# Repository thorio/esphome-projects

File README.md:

This is a loose collection of my esphome projects, including pcbs, schematics, CAD drawings and firmware where applicable.

Most don't have BOMs or assembly instructions unfortunately, as it would just eat up too much time.

Open an issue if you have questions.

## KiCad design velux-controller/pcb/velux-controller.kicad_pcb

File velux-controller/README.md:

# ESPHome Velux Controller

This project modifies a Velux KLI 310 or similar remote control to integrate with home assistant.
It replaces the back panel of the original remote, powers it from the wall, and can report state back to home assistant even if you press the physical buttons.

Installing it on the remote only requires removing the back and batteries, soldering 5 wires and plugging it into the control board. This process is nondestructive and reversible.

It runs on anywhere between 5V and 12V, though 5V is preferred.

## Bill of Materials

- 1x ESP-12F module
	([Mouser](https://eu.mouser.com/ProductDetail/Adafruit/2491?qs=N%2F3wi2MvZWDVFv7HwruvGQ%3D%3D),
	[AliExpress](https://www.aliexpress.com/item/1005004495916418.html))
- 1x SOT223 AMS1117-3.3 linear voltage regulator
	([DigiKey](https://www.digikey.com/en/products/detail/texas-instruments/TLV1117LV33DCYR/2666508),
	[AliExpress](https://www.aliexpress.com/item/1005004529378722.html))
- 3x SOT23 MMBT3904 transistor
	([DigiKey](https://www.digikey.com/en/products/detail/diotec-semiconductor/MMBT3904/20391048),
	[AliExpress](https://www.aliexpress.com/item/1005002334131697.html))
- 8x 0603 10kΩ resistor
	([DigiKey](https://www.digikey.com/en/products/detail/stackpole-electronics-inc/RMCF0603FT10K0/1761235),
	[AliExpress](https://www.aliexpress.com/item/32867298442.html))
- 6x 0603 1kΩ resistor
	([DigiKey](https://www.digikey.com/en/products/detail/stackpole-electronics-inc/RMCF0603FT1K00/1761077),
	[AliExpress](https://www.aliexpress.com/item/32867298442.html))
- 2x 0805 100nF ceramic capacitor
	([DigiKey](https://www.digikey.com/en/products/detail/samsung-electro-mechanics/CL21B104KACNNNC/3886757),
	[AliExpress](https://www.aliexpress.com/item/32964553793.html))
- 1x SMA 22μF tantalum capacitor
	([DigiKey](https://www.digikey.com/en/products/detail/kemet/T491A226M010AT/818553),
	[AliExpress](https://www.aliexpress.com/item/1005006136419609.html))
- 2x PTS820 tactile switch
	([DigiKey](https://www.digikey.com/en/products/detail/cit-relay-and-switch/CS1213AGF160/16607723),
	[AliExpress](https://www.aliexpress.com/item/1005004307665595.html))
- 1x DC-005 jack
	([DigiKey](https://www.digikey.com/en/products/detail/tensility-international-corp/54-00166/10459294),
	[AliExpress](https://www.aliexpress.com/item/4001206395694.html))
- 1x male pin header 1x4 2.54mm pitch
	([AliExpress](https://www.aliexpress.com/item/4000857385112.html))
- 1x 2Pin JST-XH connector pair, right angle
	([DigiKey](https://www.digikey.com/en/products/detail/jst-sales-america-inc/S2B-XH-A-1/9961922),
	AliExpress [assortment](https://www.aliexpress.com/item/1005006498660940.html) + [right angle](https://www.aliexpress.com/item/1005004067623293.html))
- 1x 3Pin JST-XH connector pair, right angle
	([DigiKey](https://www.digikey.com/en/products/detail/jst-sales-america-inc/S3B-XH-A-1/1556255),
	AliExpress [assortment](https://www.aliexpress.com/item/1005006498660940.html) + [right angle](https://www.aliexpress.com/item/1005004067623293.html))
- spare wire + JST-XH crimps
	([AliExpress assortment](https://www.aliexpress.com/item/1005006498660940.html))
- 4x M2x6mm coarse thread screws, pan head
	([AliExpress](https://www.aliexpress.com/item/33043885403.html))
- 4x M2 paper washers
	([AliExpress](https://www.aliexpress.com/item/1005003052657995.html))

I didn't need these, but you can add them if your ESP is unhappy with the supply voltage:

> Note: It isn't super obvious from the footprints, but these additional capacitors are supposed to mount horizontally against the board facing toward the bottom. If mounted vertically they may prevent the case from being closed.

- 1x 470μF >=5V electrolytic capacitor, 2mm pitch
	([DigiKey](https://www.digikey.com/en/products/detail/wurth-elektronik/860010273011/5726952),
	[AliExpress assortment](https://www.aliexpress.com/item/1940215752.html))
- 1x 10μF >=16V electrolytic capacitor, 1.5mm pitch
	([DigiKey](https://www.digikey.com/en/products/detail/nichicon/UVR1C100MDD6TP/4328964),
	[AliExpress assortment](https://www.aliexpress.com/item/1940215752.html))

## Attribution
Thanks to these fine people for their research on how to interface with the remote control:
- https://ottelo.jimdofree.com/velux-integra-esp8266/
- https://www.reddit.com/r/homeassistant/comments/pzhkia/hack_velux_kli3xx_to_use_blinds_without_gateway/

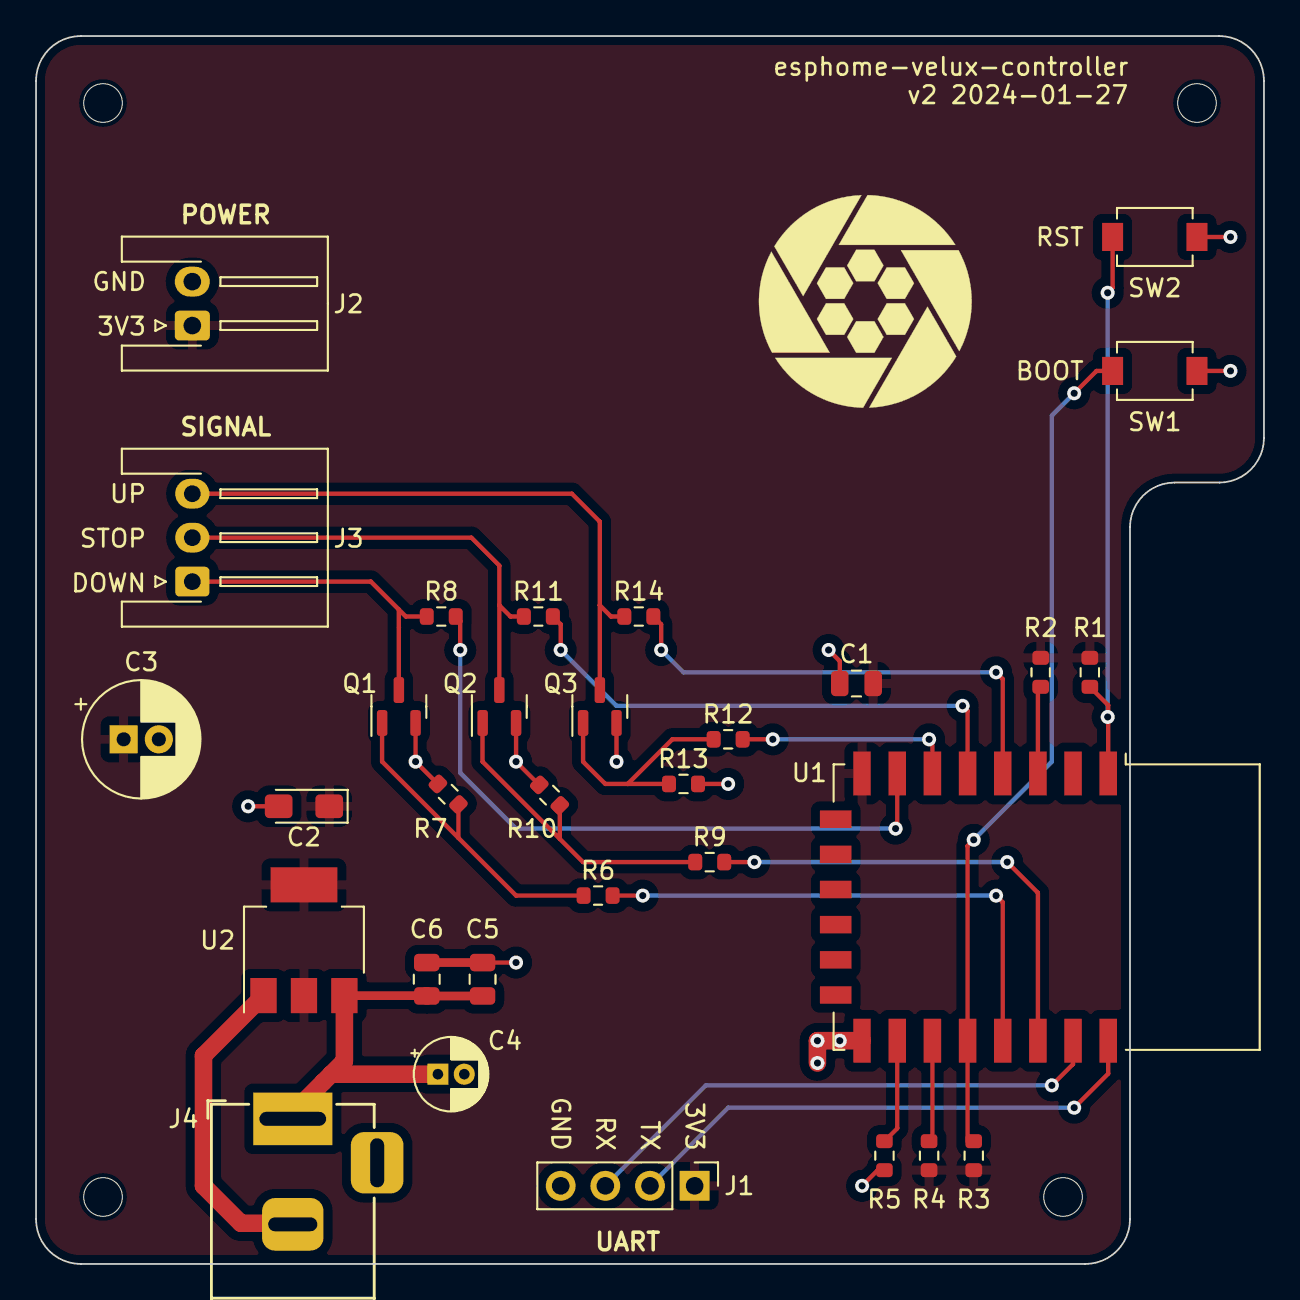
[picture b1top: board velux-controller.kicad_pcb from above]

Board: 2 copper layers, 69.9 x 69.8 mm, 35 parts (0 on the bottom side), 22 nets.

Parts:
C1, C6: 0.1μF; C_0805_2012Metric
C2: 22μF; CP_EIA-3216-10_Kemet-I_Pad1.58x1.35mm_HandSolder
C3: 470μF; CP_Radial_D6.5mm_P2.00mm
C4: 10μF; CP_Radial_D4.0mm_P1.50mm
C5: 10μF; C_0805_2012Metric
H1, H2, H3, H4: MountingHole; MountingHole_2.2mm_M2
J1: UART; PinHeader_1x04_P2.54mm_Vertical
J2: POWER; JST_XH_S2B-XH-A-1_1x02_P2.50mm_Horizontal
J3: SIGNAL; JST_XH_S3B-XH-A-1_1x03_P2.50mm_Horizontal
J4: PWR; DC_barrel_jack_2.1mm
Q1, Q2, Q3: MMBT3904; SOT-23
R1, R2, R3, R4, R5, R7, R10, R13: 10K; R_0603_1608Metric
R6, R8, R9, R11, R12, R14: 1K; R_0603_1608Metric
SW1: BOOT; SW_PTS820
SW2: RST; SW_PTS820
U1: ESP-12F; ESP-12E
U2: AMS1117-3.3; SOT-223-3_TabPin2

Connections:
+3.3V: C1.2, C2.1, C3.1, J1.1, J2.1, R1.2, R2.2, R3.2, R4.2, U1.8 (VCC), U2.2 (VO)
/EN: R2.1, U1.3 (EN)
/GPIO0: R3.1, SW1.2, U1.18 (GPIO0)
/GPIO2: R4.1, U1.17 (GPIO2)
/GPIO4: R6.2, U1.19 (GPIO4)
/GPIO5: R9.2, U1.20 (GPIO5)
/GPIO12: R12.2, U1.6 (GPIO12)
/GPIO13: R8.2, U1.7 (GPIO13)
/GPIO14: R11.2, U1.5 (GPIO14)
/GPIO15: R5.2, U1.16 (GPIO15)
/GPIO16: R14.2, U1.4 (GPIO16)
/LINE_DOWN: J3.1, Q1.3 (C), R8.1
/LINE_STOP: J3.2, Q2.3 (C), R11.1
/LINE_UP: J3.3, Q3.3 (C), R14.1
/RST: R1.1, SW2.2, U1.1 (~RST)
/RXD: J1.3, U1.21 (GPIO3/RXD)
/TXD: J1.2, U1.22 (GPIO1/TXD)
GND: C1.1, C2.2, C3.2, C4.2, C5.1, C6.1, J1.4, J2.2, J4.2, Q1.2 (E), Q2.2 (E), Q3.2 (E), R5.1, R7.2, R10.2, R13.2, SW1.1, SW2.1, U1.15 (GND), U2.1 (GND)
unnamed: Q1.1 (B), R6.1, R7.1
unnamed: Q2.1 (B), R9.1, R10.1
unnamed: Q3.1 (B), R12.1, R13.1
VCC: C4.1, C5.2, C6.2, J4.1, U2.3 (VI)

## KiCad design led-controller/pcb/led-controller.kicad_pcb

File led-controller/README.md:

# ESPHome LED Controller

Controls either individually addressible or single-color "dumb" LED strips, with an optional button or rotary encoder.
This means I effectively get four different controller options in one PCB order.

It can use either 12V or 5V LED strips, running the controller off the same power supply as the LEDs.

### WARNING: I didn't properly engineer this, so I don't know how much current it can safely push. Use at your own risk.

### Variants

Depending on the configuration, different parts must be printed and different components soldered to the board:

**Input**: Solder either the push-button or the rotary encoder, and print the appropriate covers for the housing.

**Output**: Solder either:
- the mosfet U1 for PWM control of "dumb" LEDs or
- the resistor R6 and the jumper JP1 for controlling individually addressible LEDs.

Depending on the configuration chosen, the firmware must be modified as well. See the comments in `firmware.yml`.

NOTE: I had to rip out some of the reference models from the Fusion 360 CAD drawings because I don't have the rights to them.
This leaves the references all jumbled, sorry about that.

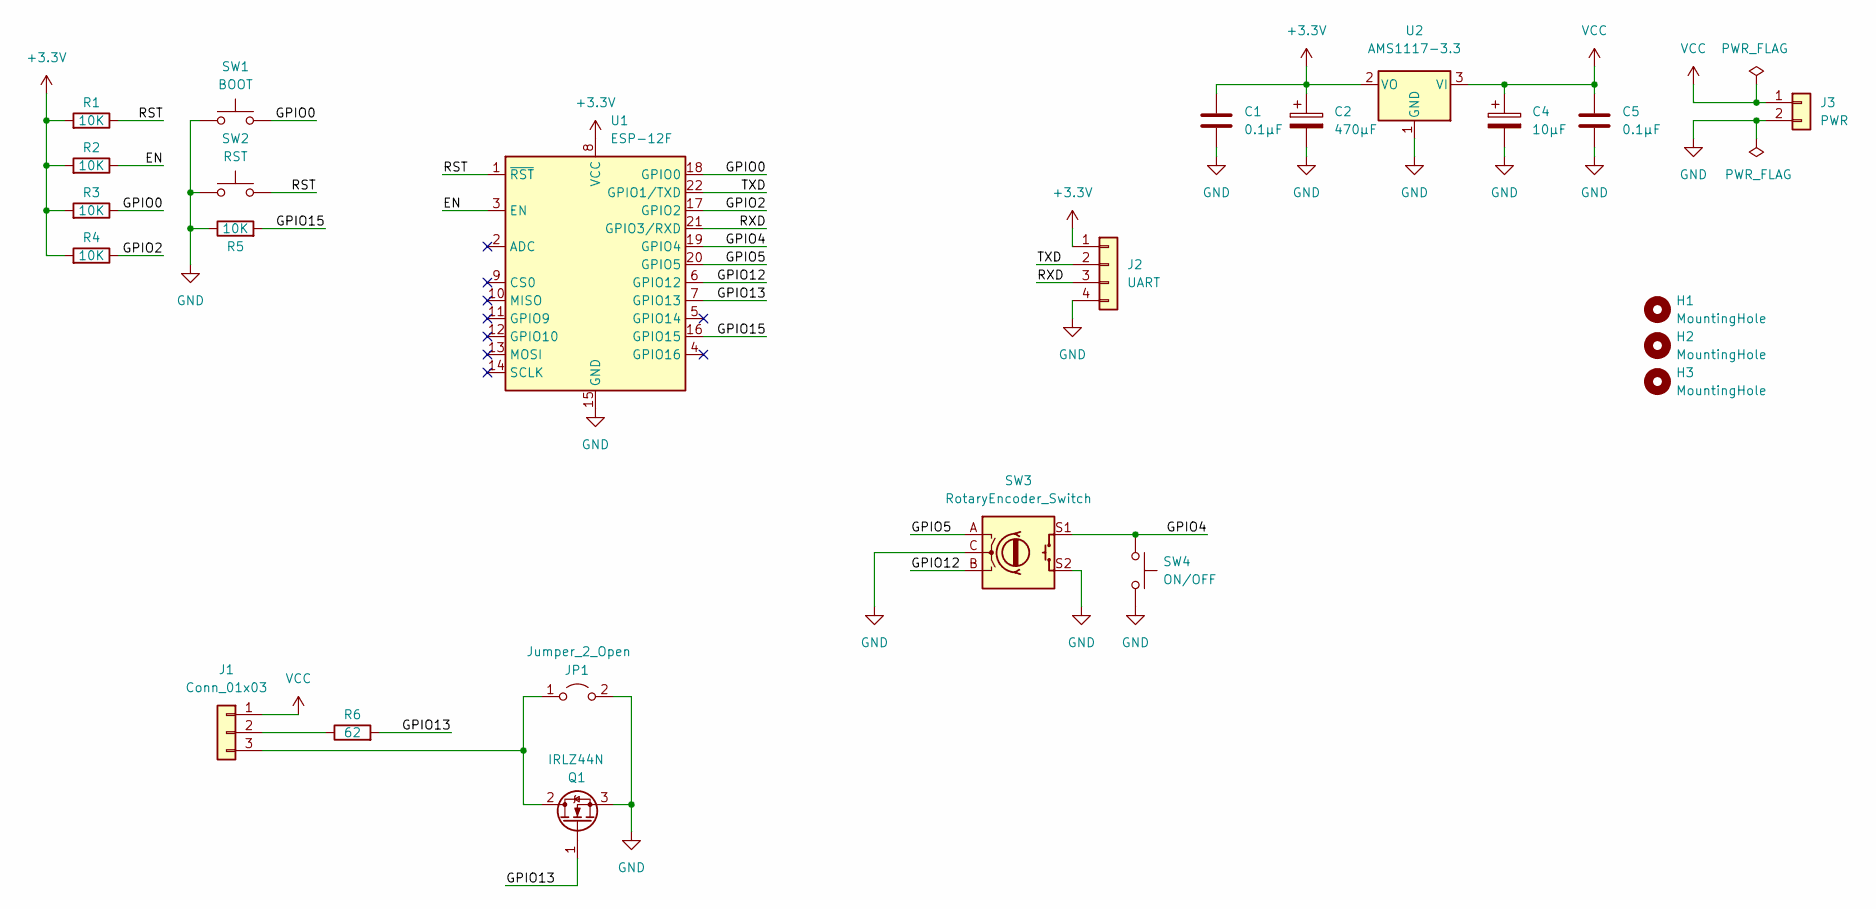
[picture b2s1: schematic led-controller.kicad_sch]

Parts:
C1, C5: 0.1μF; C_0805_2012Metric
C2: 470μF; CP_Radial_D6.5mm_P2.00mm
C4: 10μF; CP_Radial_D4.0mm_P1.50mm
H1, H2, H3: MountingHole; MountingHole_2.2mm_M2
J1: Conn_01x03; TerminalBlock_KF301-3P-5mm
J2: UART; PinHeader_1x04_P2.54mm_Vertical
J3: PWR; TerminalBlock_KF301-2P-5mm
JP1: Jumper_2_Open; SolderWire-1.5sqmm_1x02_P6mm_D1.7mm_OD3mm
Q1: IRLZ44N; TO-220-3_Horizontal_TabDown
R1, R2, R3, R4, R5: 10K; R_0603_1608Metric
R6: 62; R_0603_1608Metric
SW1: BOOT; SW_PTS820
SW2: RST; SW_PTS820
SW3: RotaryEncoder_Switch; RotaryEncoder_Alps_EC11E-Switch_Vertical_H20mm
SW4: ON/OFF; SW_SPST_TL3342
U1: ESP-12F; ESP-12E
U2: AMS1117-3.3; SOT-223-3_TabPin2

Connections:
+3.3V: C1.2, C2.1, J2.1, R1.2, R2.2, R3.2, R4.2, U1.8 (VCC), U2.2 (VO)
/EN: R2.1, U1.3 (EN)
/GPIO0: R3.1, SW1.2, U1.18 (GPIO0)
/GPIO2: R4.1, U1.17 (GPIO2)
/GPIO4: SW3.S1, SW4.1, U1.19 (GPIO4)
/GPIO5: SW3.A, U1.20 (GPIO5)
/GPIO12: SW3.B, U1.6 (GPIO12)
/GPIO13: Q1.1 (G), R6.2, U1.7 (GPIO13)
/GPIO15: R5.2, U1.16 (GPIO15)
/RST: R1.1, SW2.2, U1.1 (~RST)
/RXD: J2.3, U1.21 (GPIO3/RXD)
/TXD: J2.2, U1.22 (GPIO1/TXD)
GND: C1.1, C2.2, C4.2, C5.1, J2.4, J3.2, JP1.2 (B), Q1.3 (S), R5.1, SW1.1, SW2.1, SW3.C, SW3.S2, SW4.2, U1.15 (GND), U2.1 (GND)
unnamed: J1.2, R6.1
unnamed: J1.3, JP1.1 (A), Q1.2 (D)
VCC: C4.1, C5.2, J1.1, J3.1, U2.3 (VI)

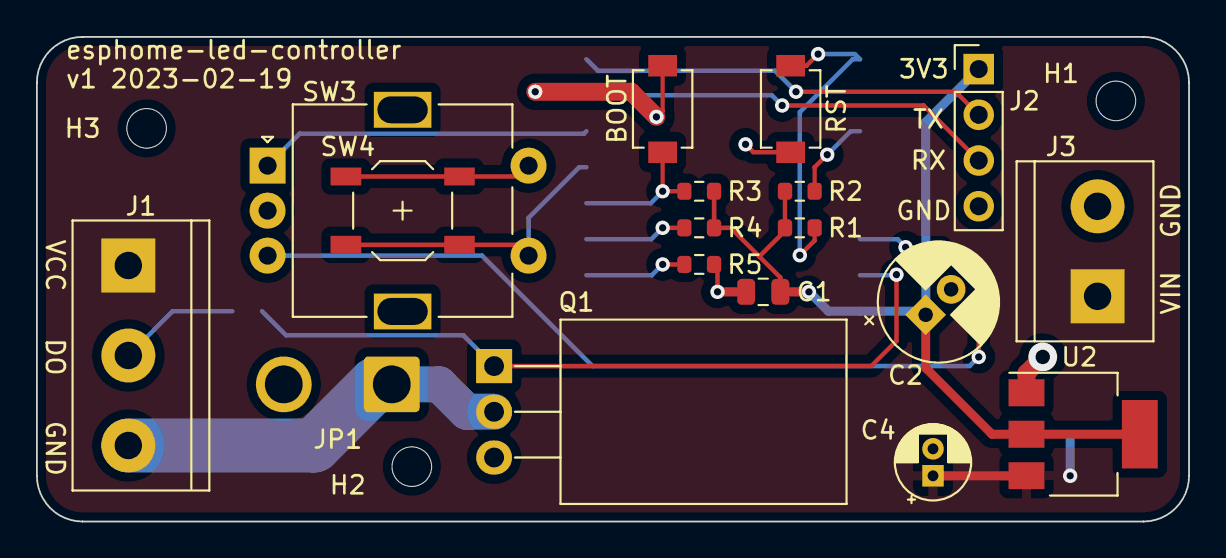
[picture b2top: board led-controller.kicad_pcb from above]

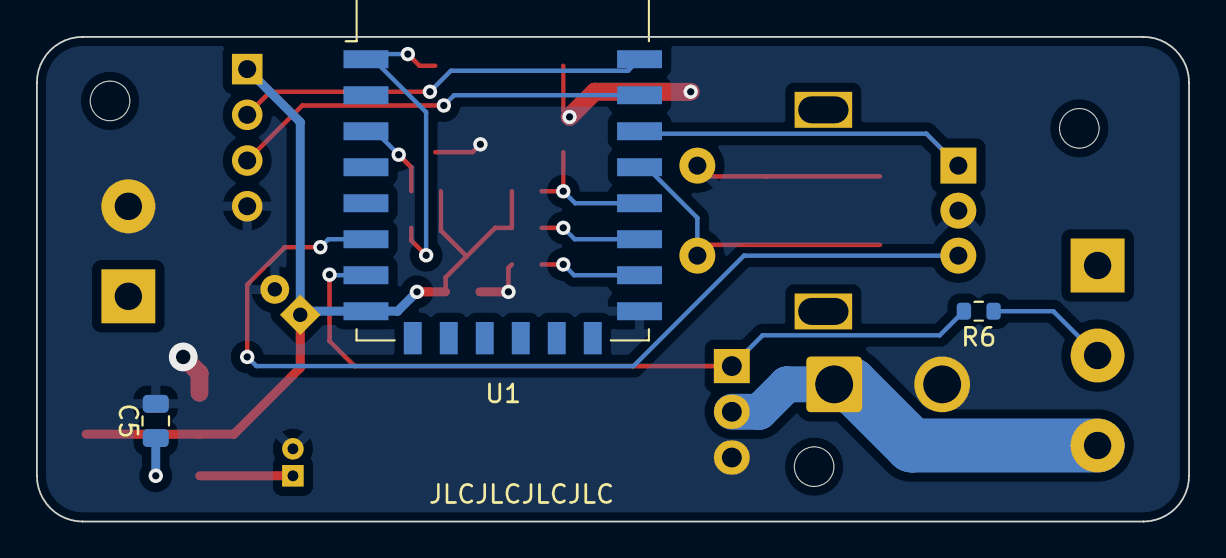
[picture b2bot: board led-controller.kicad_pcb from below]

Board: 2 copper layers, 64.0 x 26.9 mm, 24 parts (3 on the bottom side), 16 nets.

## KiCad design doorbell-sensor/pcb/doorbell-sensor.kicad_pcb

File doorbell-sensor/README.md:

# ESPHome Doorbell Sensor

This board is meant to go inside your doorbell/intercom (the old-school ones with a phone) and detect when the doorbell rings.
It uses an optocoupler to minimize modification to the existing electronics.

For now, I can't recommend using this with the ESP-01S as I've had connectivity issues.
I might redesign it to use an ESP-12F module in the future though.

No CAD drawings for this one, I just designed a super simple mounting plate that I glued to the intercom housing and seem to have deleted it afterwards.

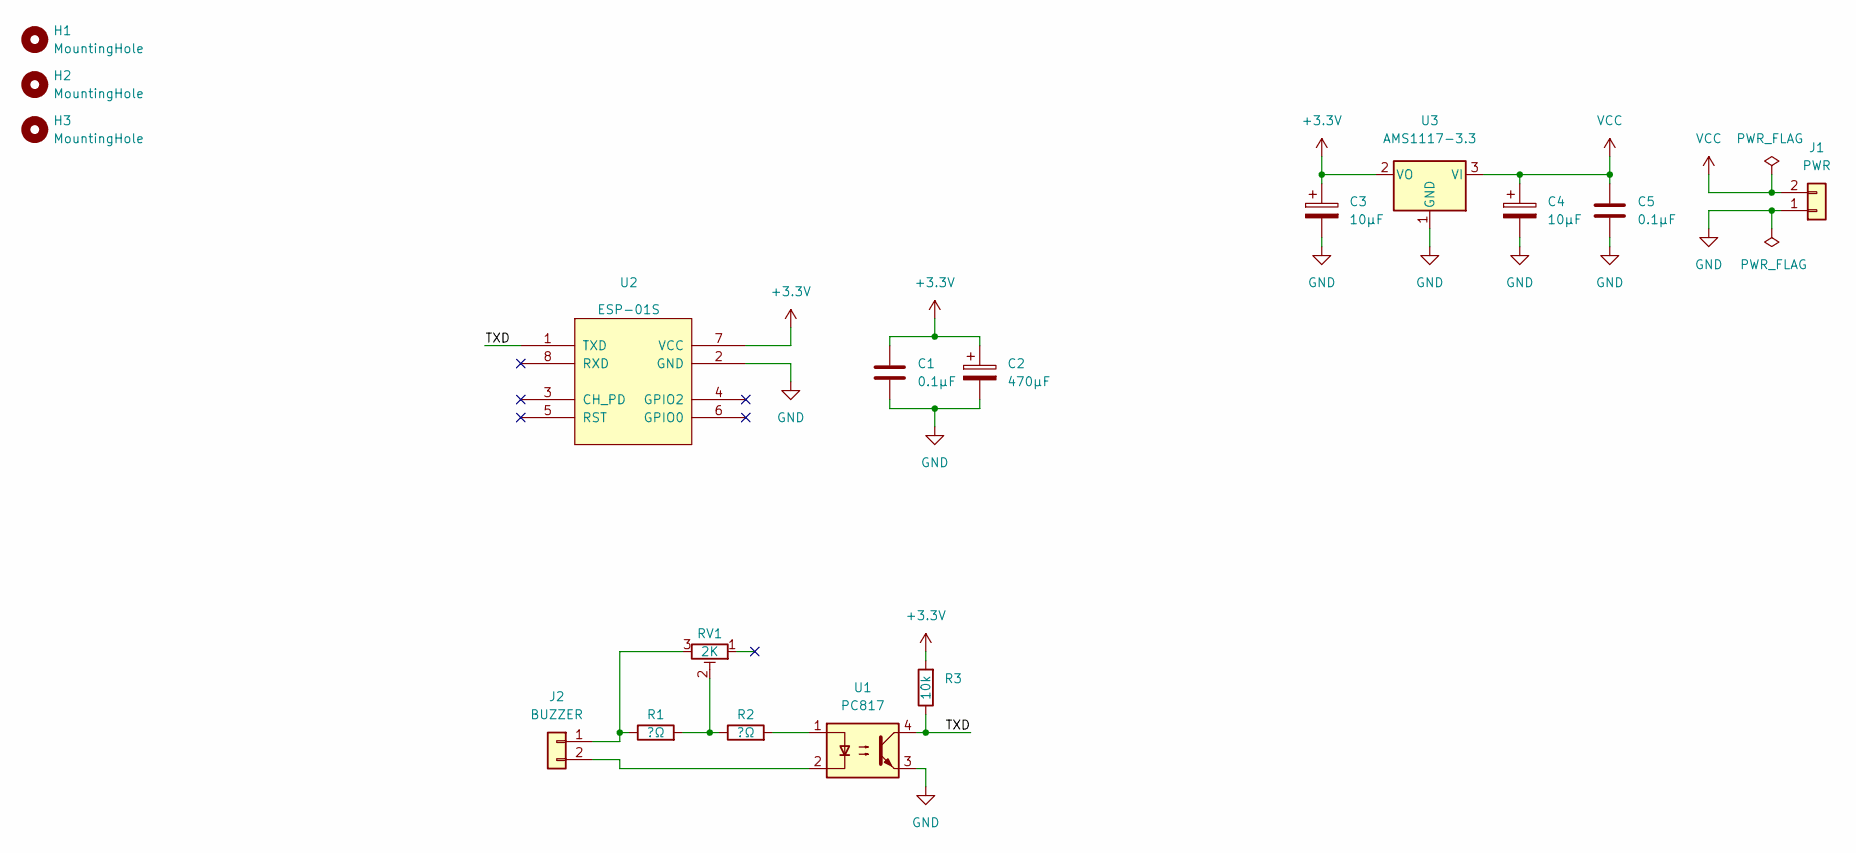
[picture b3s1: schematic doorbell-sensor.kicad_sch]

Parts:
C1, C5: 0.1μF; C_0805_2012Metric
C2: 470μF; CP_Radial_D10.0mm_P2.50mm_P5.00mm
C3, C4: 10μF; CP_Radial_D4.0mm_P1.50mm
H1, H2, H3: MountingHole; MountingHole_2.2mm_M2
J1: PWR; TerminalBlock_KF301-2P-5mm
J2: BUZZER; TerminalBlock_KF301-2P-5mm
R1, R2: ?Ω; R_0603_1608Metric
R3: 10k; R_0603_1608Metric
RV1: 2K; Potentiometer_Runtron_RM-065_Vertical
U1: PC817; DIP-4_W7.62mm
U2: ESP-01S; ESP-01
U3: AMS1117-3.3; SOT-223-3_TabPin2

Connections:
+3.3V: C1.2, C2.1, C3.1, R3.2, U2.7 (VCC), U3.2 (VO)
/TXD: R3.1, U1.4, U2.1 (TXD)
GND: C1.1, C2.2, C3.2, C4.2, C5.1, J1.1, U1.3, U2.2 (GND), U3.1 (GND)
unnamed: J2.1, R1.1, RV1.3
unnamed: J2.2, U1.2
unnamed: R1.2, R2.1, RV1.2
unnamed: R2.2, U1.1
VCC: C4.1, C5.2, J1.2, U3.3 (VI)

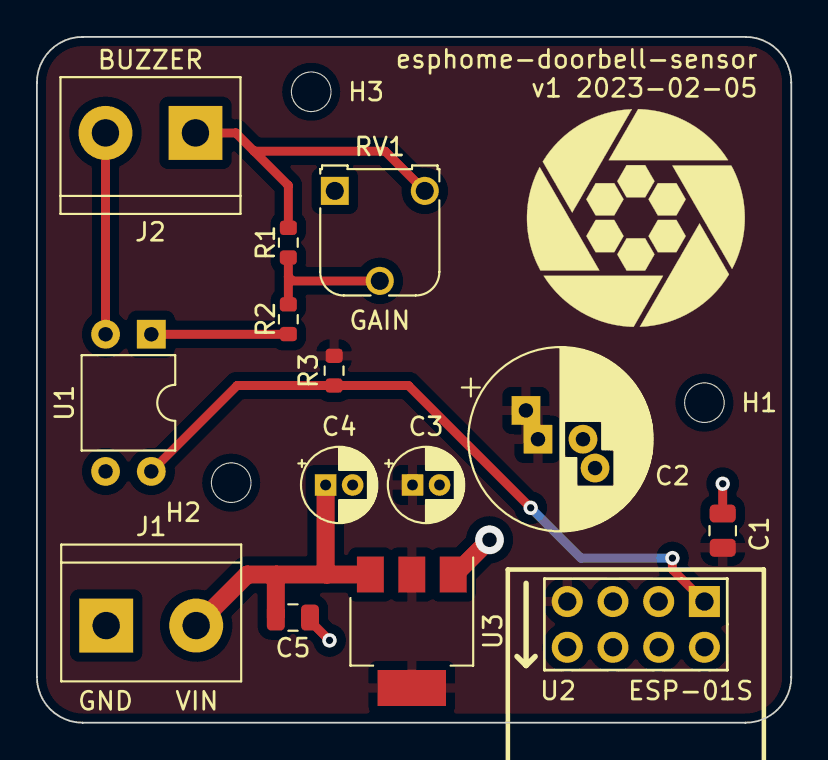
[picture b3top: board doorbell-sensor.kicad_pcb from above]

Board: 2 copper layers, 41.9 x 38.1 mm, 17 parts (0 on the bottom side), 8 nets.

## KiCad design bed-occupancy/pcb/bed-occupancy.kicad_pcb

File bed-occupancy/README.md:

# bed-occupancy

My first PCB design, very basic, using exclusively THT components and mostly pre-build modules.

This is mostly for archival purposes; I can't recommend using the ESP-01S as I've had connectivity issues.

I had to rip out some of the reference models from the Fusion 360 CAD drawings because I don't have the rights to them.
This leaves the references all jumbled, sorry about that.

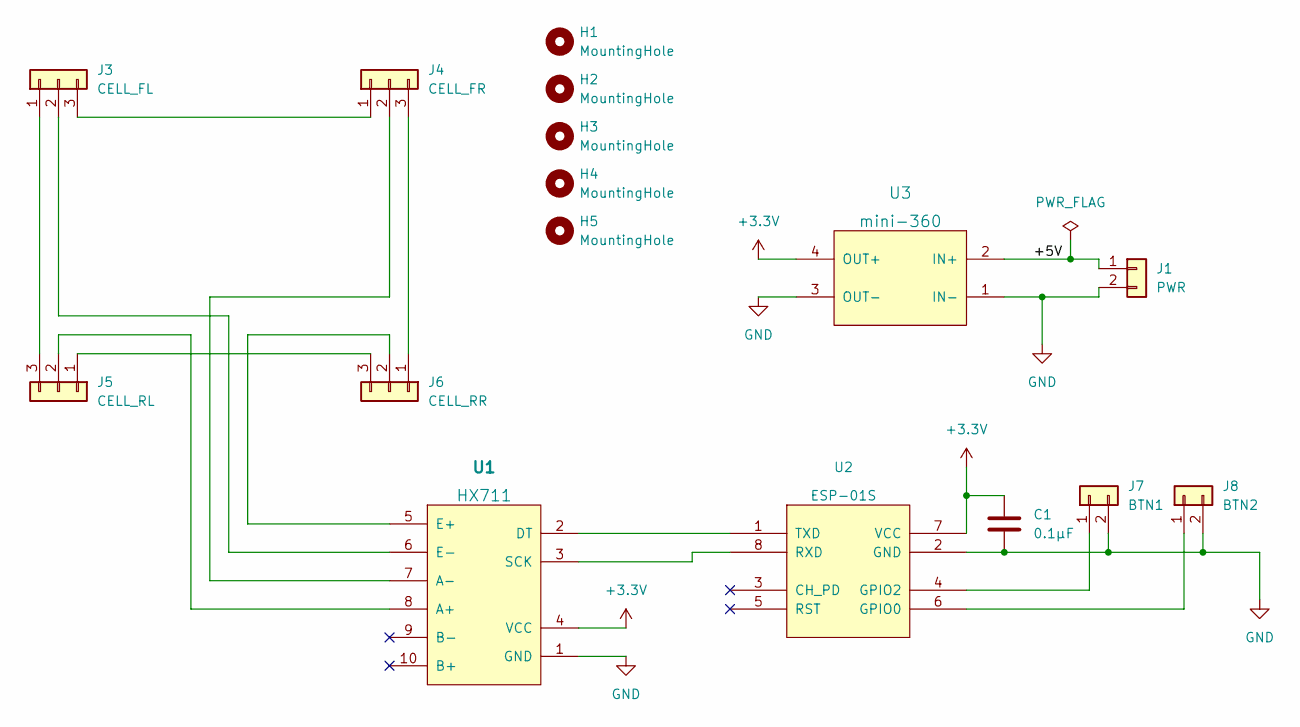
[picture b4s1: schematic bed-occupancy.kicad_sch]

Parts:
C1: 0.1μF; C_Disc_D5.0mm_W2.5mm_P2.50mm
H1, H2, H3, H4, H5: MountingHole; MountingHole_2.2mm_M2
J1: PWR; JST_XH_B2B-XH-A_1x02_P2.50mm_Vertical
J3: CELL_FL; JST_XH_B3B-XH-A_1x03_P2.50mm_Vertical
J4: CELL_FR; JST_XH_B3B-XH-A_1x03_P2.50mm_Vertical
J5: CELL_RL; JST_XH_B3B-XH-A_1x03_P2.50mm_Vertical
J6: CELL_RR; JST_XH_B3B-XH-A_1x03_P2.50mm_Vertical
J7: BTN1; JST_XH_B2B-XH-A_1x02_P2.50mm_Vertical
J8: BTN2; JST_XH_B2B-XH-A_1x02_P2.50mm_Vertical
U1: HX711
U2: ESP-01S; ESP-01
U3: mini-360

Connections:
+3.3V: C1.2, U1.4 (VCC), U2.7 (VCC), U3.4 (OUT+)
/+5V: J1.1, U3.2 (IN+)
GND: C1.1, J1.2, J7.2, J8.2, U1.1 (GND), U2.2 (GND), U3.1 (IN-), U3.3 (OUT-)
unnamed: J3.1, J5.3
unnamed: J3.2, U1.6 (E-)
unnamed: J3.3, J4.1
unnamed: J4.2, U1.7 (A-)
unnamed: J4.3, J6.1
unnamed: J5.1, J6.3
unnamed: J5.2, U1.8 (A+)
unnamed: J6.2, U1.5 (E+)
unnamed: J7.1, U2.4 (GPIO2)
unnamed: J8.1, U2.6 (GPIO0)
unnamed: U1.2 (DT), U2.1 (TXD)
unnamed: U1.3 (SCK), U2.8 (RXD)

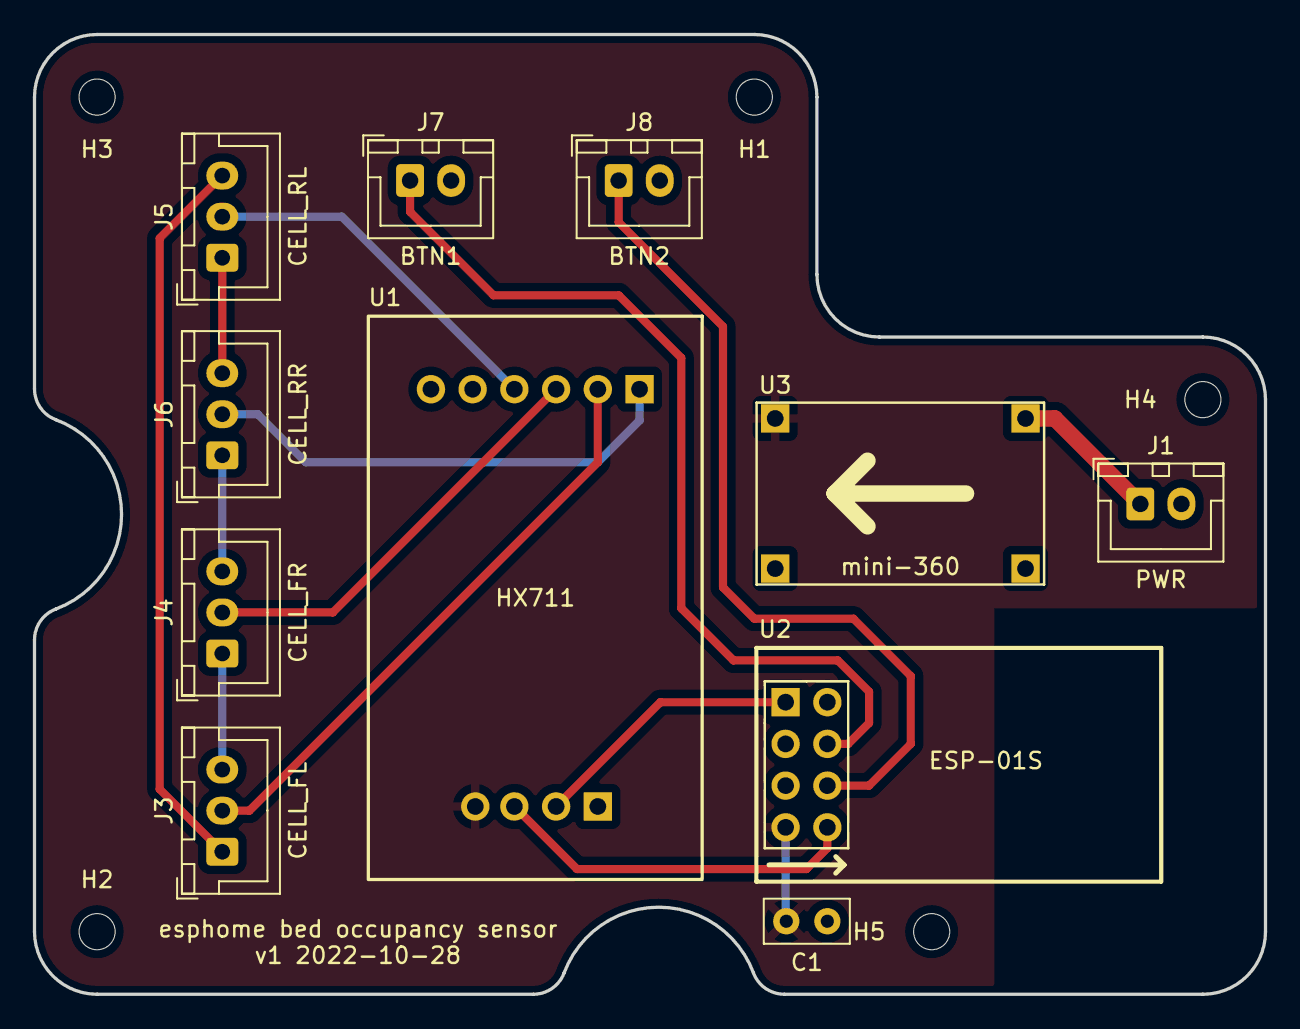
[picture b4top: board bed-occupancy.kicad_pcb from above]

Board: 2 copper layers, 74.9 x 58.4 mm, 16 parts (0 on the bottom side), 15 nets.

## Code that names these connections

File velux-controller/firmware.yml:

esphome:
  name: esphome-velux-controller
  friendly_name: ESPHome velux-controller

esp8266:
  board: esp01_1m

logger:

api:
  encryption:
    key: "your_secret_here"

ota:
  password: "your_secret_here"

wifi:
  ssid: !secret wifi_ssid
  password: !secret wifi_password

# Globals to track position and movement
globals:
  - id: shutter_position
    type: float
    restore_value: true
    initial_value: '0.0'  # 0.0 = closed, 1.0 = open
  - id: last_direction
    type: int
    restore_value: true
    initial_value: '0'  # 0 = stop, 1 = opening, -1 = closing
  - id: movement_start_time
    type: unsigned long
    initial_value: '0'
  - id: target_position
    type: float
    initial_value: '0.0'  # Desired end position
    
switch:
  - platform: gpio
    id: output_up
    pin: GPIO12
    on_turn_on:
      then:
        - delay: 200ms
        - switch.turn_off: output_up
  - platform: gpio
    id: output_stop
    pin: GPIO5
    on_turn_on:
      then:
        - delay: 200ms
        - switch.turn_off: output_stop
  - platform: gpio
    id: output_down
    pin: GPIO4
    on_turn_on:
      then:
        - delay: 200ms
        - switch.turn_off: output_down

# These pins are connected to the output, and will be low if either:
# - We set the output pins
# - Someone presses the physical buttons on the original remote
#
# To avoid interference from ourselves, we ignore the input pins
# if we're the ones driving the output low.
binary_sensor:
  - platform: gpio
    id: sense_up
    pin: GPIO16
    filters:
      - lambda: !lambda return !(x || id(output_up).state);
    on_press:
      then:
        - cover.open: shutters
  - platform: gpio
    id: sense_stop
    pin: GPIO14
    filters:
      - lambda: !lambda return !(x || id(output_stop).state);
    on_press:
      then:
        - cover.stop: shutters
  - platform: gpio
    id: sense_down
    pin: GPIO13
    filters:
      - lambda: !lambda return !(x || id(output_down).state);
    on_press:
      then:
        - cover.close: shutters

# Template cover that tracks position accurately
cover:
  - platform: template
    id: shutters
    name: Window Shutters
    has_position: true
    
    # Simple function to report current position
    lambda: |-
      return id(shutter_position);
    
    open_action:
      - lambda: |-
          id(last_direction) = 1;
          id(movement_start_time) = millis();
          id(target_position) = 1.0;  // Fully open
      - switch.turn_on: output_up
      
    close_action:
      - lambda: |-
          id(last_direction) = -1;
          id(movement_start_time) = millis();
          id(target_position) = 0.0;  // Fully closed
      - switch.turn_on: output_down
      
    stop_action:
      - lambda: |-
          id(last_direction) = 0;
      - switch.turn_on: output_stop
      
    position_action:
      - lambda: |-
          float target = pos;
          float current = id(shutter_position);
          
          // Always update target position, even during movement
          id(target_position) = target;
          
          // If we're already moving in the right direction, just update target
          if (id(last_direction) == 1 && target > current) {
            // Already opening and target is higher - just update target
            return;
          } else if (id(last_direction) == -1 && target < current) {
            // Already closing and target is lower - just update target  
            return;
          }
          
          // Stop current movement first if we need to change direction
          if (id(last_direction) != 0) {
            // Update current position before changing direction
            unsigned long now = millis();
            float elapsed = (now - id(movement_start_time)) / 1000.0;
            float movement = elapsed / 18.0;
            
            if (id(last_direction) == 1) {
              id(shutter_position) = min(1.0f, id(shutter_position) + movement);
            } else if (id(last_direction) == -1) {
              id(shutter_position) = max(0.0f, id(shutter_position) - movement);
            }
            
            // Brief stop before changing direction
            id(output_stop).turn_on();
          }
          
          // Determine new direction
          current = id(shutter_position); // Use updated position
          if (target > current + 0.01) { // Small tolerance to avoid jitter
            id(last_direction) = 1;
            id(movement_start_time) = millis();
          } else if (target < current - 0.01) {
            id(last_direction) = -1;
            id(movement_start_time) = millis();
          } else {
            // Already at target position
            id(last_direction) = 0;
            id(shutter_position) = target;
            return;
          }
      - delay: 50ms  # Brief delay after stop before new movement
      - if:
          condition:
            lambda: 'return id(last_direction) == 1;'
          then:
            - switch.turn_on: output_up
      - if:
          condition:
            lambda: 'return id(last_direction) == -1;'
          then:
            - switch.turn_on: output_down

# Single interval for all updates
interval:
  - interval: 1s  # Calculate position every 1 second
    then:
      - lambda: |-
          // Only calculate when moving
          if (id(last_direction) != 0) {
            unsigned long now = millis();
            float elapsed = (now - id(movement_start_time)) / 1000.0;
            float movement = elapsed / 18.0;  // 18 seconds for full open/close
            
            if (id(last_direction) == 1) {  // Opening
              id(shutter_position) = min(1.0f, id(shutter_position) + movement);
            } else if (id(last_direction) == -1) {  // Closing
              id(shutter_position) = max(0.0f, id(shutter_position) - movement);
            }
            
            id(movement_start_time) = now;
            
            // Check if we've reached target or end position
            bool should_stop = false;
            
            if (id(shutter_position) >= 1.0f && id(last_direction) == 1) {
              id(shutter_position) = 1.0f;
              should_stop = true;
            } else if (id(shutter_position) <= 0.0f && id(last_direction) == -1) {
              id(shutter_position) = 0.0f;
              should_stop = true;
            } else if (id(last_direction) == 1 && id(shutter_position) >= id(target_position)) {
              id(shutter_position) = id(target_position);
              should_stop = true;
            } else if (id(last_direction) == -1 && id(shutter_position) <= id(target_position)) {
              id(shutter_position) = id(target_position);
              should_stop = true;
            }
            
            if (should_stop) {
              id(last_direction) = 0;
              id(output_stop).turn_on();
            }
          }
      - if:
          condition:
            lambda: 'return id(last_direction) != 0;'
          then:
            # Single publish during movement - both position and operation
            - cover.template.publish:
                id: shutters
                position: !lambda 'return id(shutter_position);'
                current_operation: !lambda |-
                  if (id(last_direction) == 1) return COVER_OPERATION_OPENING;
                  if (id(last_direction) == -1) return COVER_OPERATION_CLOSING;
                  return COVER_OPERATION_IDLE;
          else:
            # Single publish when stopped - ensures IDLE status is sent once
            - if:
                condition:
                  lambda: |-
                    static unsigned long last_idle_publish = 0;
                    unsigned long now = millis();
                    if (now - last_idle_publish > 5000) { // Only every 5 seconds when idle
                      last_idle_publish = now;
                      return true;
                    }
                    return false;
                then:
                  - cover.template.publish:
                      id: shutters
                      position: !lambda 'return id(shutter_position);'
                      current_operation: IDLE

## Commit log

2023-11-26 Add bed occupancy
2023-11-27 Fix naming
2023-12-10 Add rest
2024-01-27 Add velux-controller
2024-02-18 Update velux controller readme
2024-02-18 Update shelly firmware
2024-02-21 Update velux-controller readme
2025-06-28 Status tracking and other bug fixes
